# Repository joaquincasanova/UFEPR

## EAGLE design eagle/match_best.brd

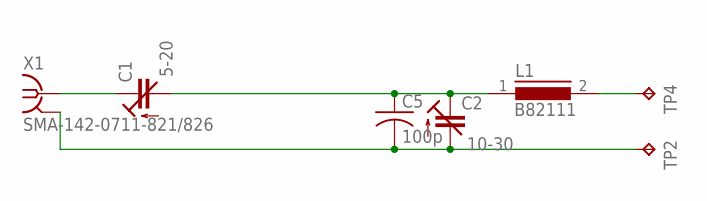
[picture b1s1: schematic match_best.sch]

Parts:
C1: 5-20; SGC3S
C2: 10-30; SGC3S
C5: 100p; 1111
L1: B82111; SUKW1-30
TP2, TP4: TPPAD1-13Y; P1-13Y
X1: SMA-142-0711-821/826; J502-ND-142-0711-821/826

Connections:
unnamed: C1.P$1 (A), C2.P$2 (E), C5.P$1 (1), L1.1
unnamed: C2.P$1 (A), C5.P$2 (2), TP2.TP, X1.G@1 (2), X1.G@2 (2), X1.G@3 (2), X1.G@4 (2)
unnamed: L1.2, TP4.TP
unnamed: C1.P$2 (E), X1.1

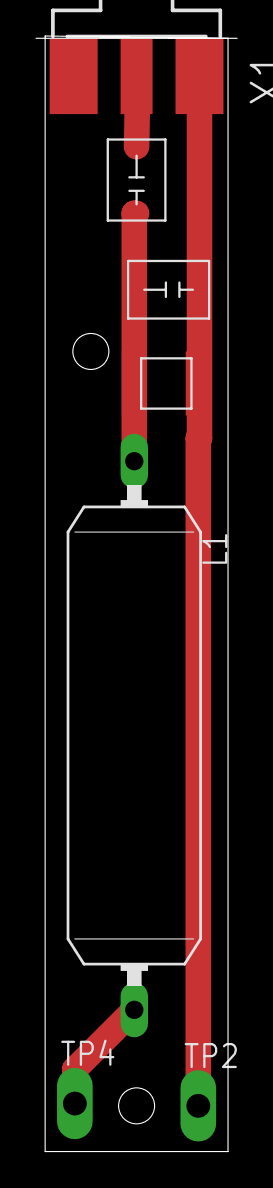
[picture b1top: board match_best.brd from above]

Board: 2 copper layers, 11.2 x 62.0 mm, 7 parts (0 on the bottom side), 4 nets.

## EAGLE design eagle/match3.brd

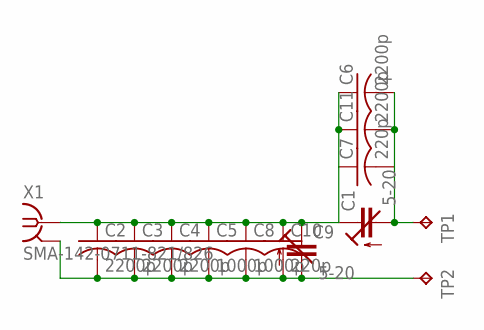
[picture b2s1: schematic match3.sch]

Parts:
C1, C9: 5-20; SGC3S
C2, C3, C4, C6, C11: 2200p; C0805
C5, C8: 1000p; C0805
C7, C10: 220p; C0805
TP1, TP2: TPPAD1-13Y; P1-13Y
X1: SMA-142-0711-821/826; J502-ND-142-0711-821/826

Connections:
unnamed: C1.P$1 (A), C6.2, C7.2, C11.2, TP1.TP
unnamed: C2.2, C3.2, C4.2, C5.2, C8.2, C9.P$1 (A), C10.2, TP2.TP, X1.G@1 (2), X1.G@2 (2), X1.G@3 (2), X1.G@4 (2)
unnamed: C1.P$2 (E), C2.1, C3.1, C4.1, C5.1, C6.1, C7.1, C8.1, C9.P$2 (E), C10.1, C11.1, X1.1

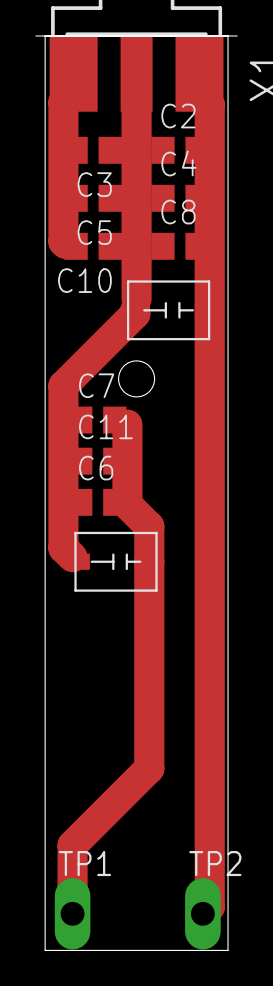
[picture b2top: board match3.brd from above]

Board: 2 copper layers, 11.2 x 50.8 mm, 14 parts (0 on the bottom side), 3 nets.

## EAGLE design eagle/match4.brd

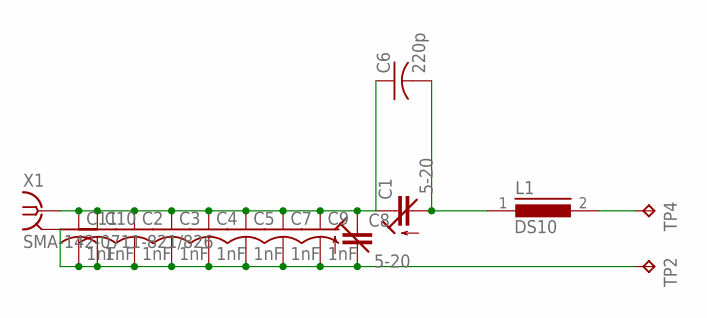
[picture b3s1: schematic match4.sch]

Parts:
C1, C8: 5-20; SGC3S
C2, C3, C4, C5, C7, C9, C10, C11: 1nF; 1111
C6: 220p; 1111
L1: DS10
TP2, TP4: TPPAD1-13Y; P1-13Y
X1: SMA-142-0711-821/826; J502-ND-142-0711-821/826

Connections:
unnamed: C1.P$1 (A), C6.P$2 (2), L1.1
unnamed: C2.P$2 (2), C3.P$2 (2), C4.P$2 (2), C5.P$2 (2), C7.P$2 (2), C8.P$1 (A), C9.P$2 (2), C10.P$2 (2), C11.P$2 (2), TP2.TP, X1.G@1 (2), X1.G@2 (2), X1.G@3 (2), X1.G@4 (2)
unnamed: L1.2, TP4.TP
unnamed: C1.P$2 (E), C2.P$1 (1), C3.P$1 (1), C4.P$1 (1), C5.P$1 (1), C6.P$1 (1), C7.P$1 (1), C8.P$2 (E), C9.P$1 (1), C10.P$1 (1), C11.P$1 (1), X1.1

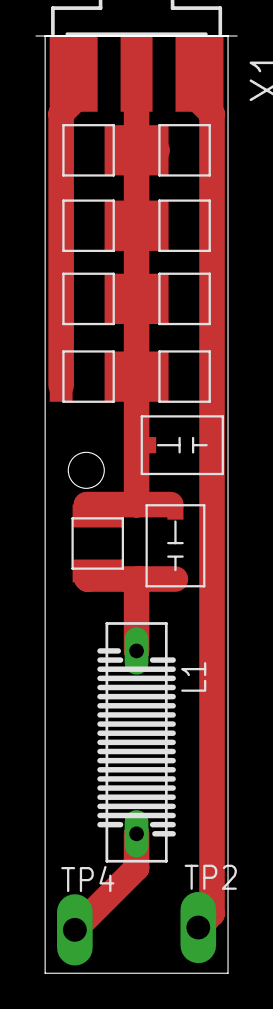
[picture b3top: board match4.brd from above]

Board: 2 copper layers, 11.2 x 52.1 mm, 15 parts (0 on the bottom side), 4 nets.

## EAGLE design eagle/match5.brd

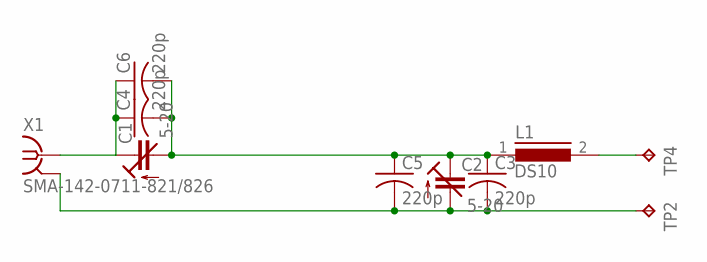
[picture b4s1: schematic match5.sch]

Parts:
C1, C2: 5-20; SGC3S
C3, C4, C5, C6: 220p; C0805
L1: DS10
TP2, TP4: TPPAD1-13Y; P1-13Y
X1: SMA-142-0711-821/826; J502-ND-142-0711-821/826

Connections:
unnamed: C1.P$1 (A), C2.P$2 (E), C3.1, C4.2, C5.1, C6.2, L1.1
unnamed: C2.P$1 (A), C3.2, C5.2, TP2.TP, X1.G@1 (2), X1.G@2 (2), X1.G@3 (2), X1.G@4 (2)
unnamed: L1.2, TP4.TP
unnamed: C1.P$2 (E), C4.1, C6.1, X1.1

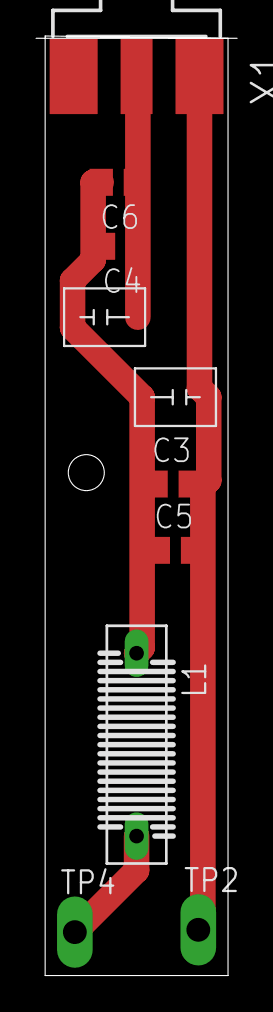
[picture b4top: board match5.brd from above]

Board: 2 copper layers, 11.2 x 52.2 mm, 10 parts (0 on the bottom side), 4 nets.

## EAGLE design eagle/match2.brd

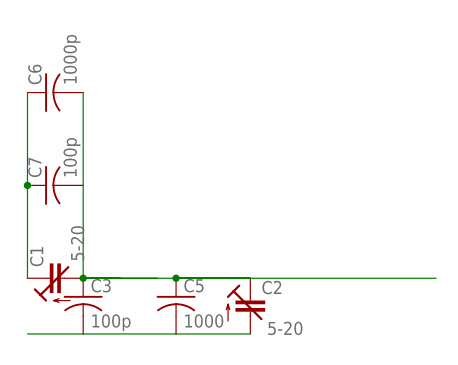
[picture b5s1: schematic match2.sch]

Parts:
C1, C2: 5-20; SGC3S
C3, C7: 100p; C0603
C5: 1000; C0805
C6: 1000p; C0805

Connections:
unnamed: C1.P$1 (A), C2.P$2 (E), C3.1, C5.1, C6.2, C7.2
unnamed: C2.P$1 (A), C3.2, C5.2
unnamed: C1.P$2 (E), C6.1, C7.1

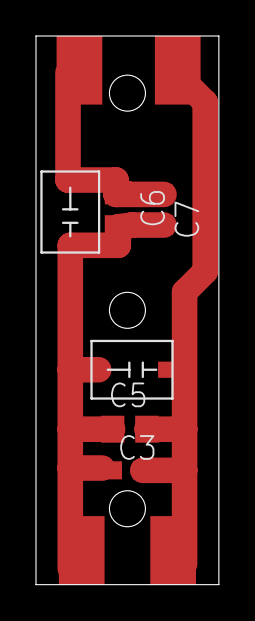
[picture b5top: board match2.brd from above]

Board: 2 copper layers, 10.2 x 30.5 mm, 6 parts (0 on the bottom side), 3 nets.

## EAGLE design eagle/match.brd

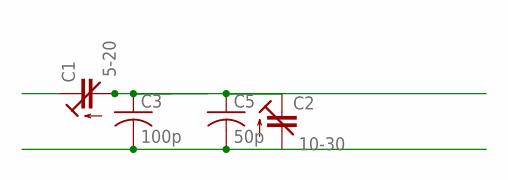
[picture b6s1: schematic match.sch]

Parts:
C1: 5-20; SGC3S
C2: 10-30; SGC3S
C3: 100p; C0805
C5: 50p; C0805

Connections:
unnamed: C1.P$1 (A), C2.P$2 (E), C3.1, C5.1
unnamed: C3.2, C5.2

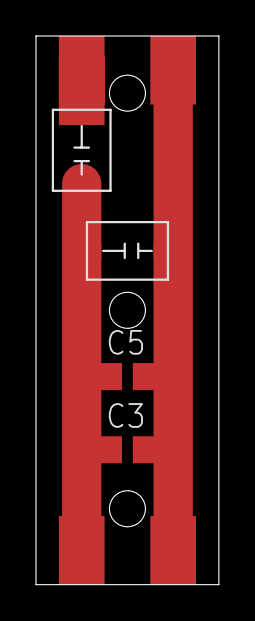
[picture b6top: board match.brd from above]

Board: 2 copper layers, 10.2 x 30.5 mm, 4 parts (0 on the bottom side), 2 nets.

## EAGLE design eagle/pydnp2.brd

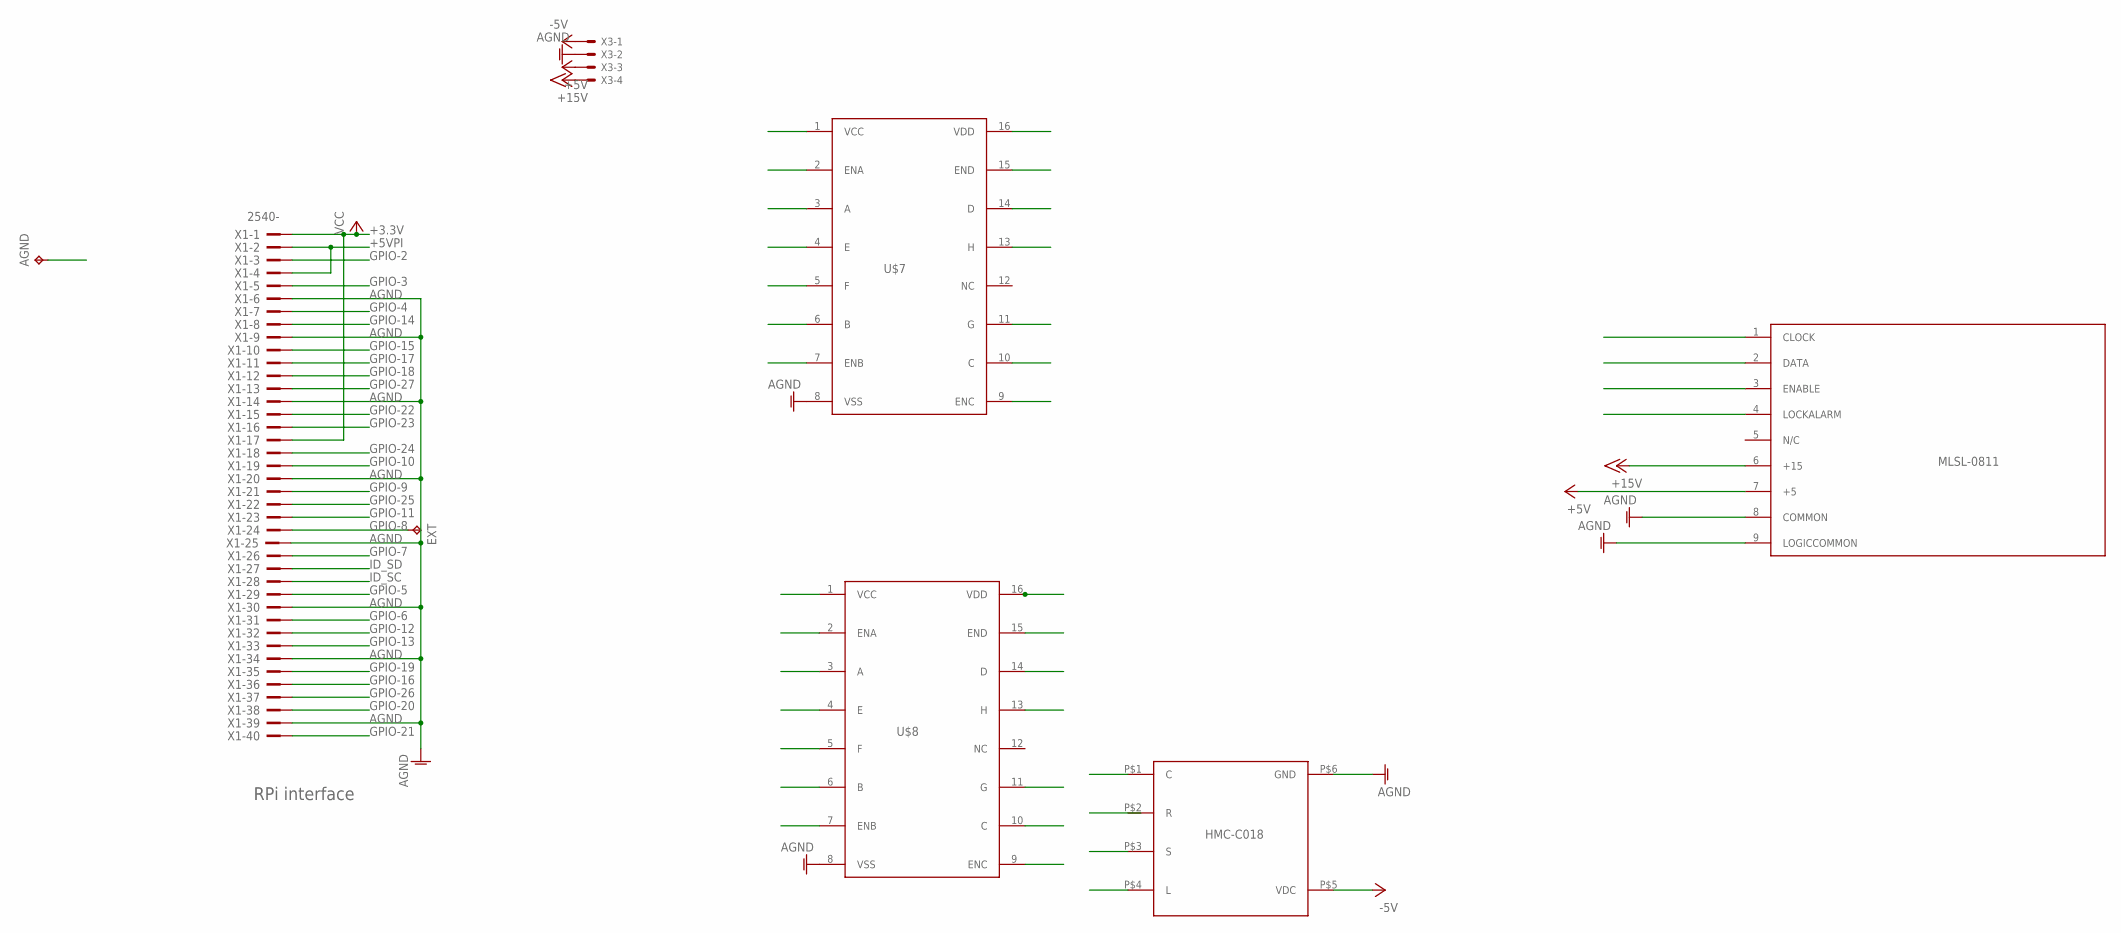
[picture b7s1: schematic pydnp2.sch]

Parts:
AGND: TPPAD1-20Y; P1-20Y
EXT: TPPAD1-20Y; P1-20Y
U$1: MLSLCORRECT; 177-009-FEMALE
U$2: HMC-C018
U$7, U$8: 40109; DIL16
X1: 2540-; PAK100/2500-40
X3: KK-156-4

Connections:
+3.3V: U$7.1 (VCC), U$7.2 (ENA), U$7.7 (ENB), U$7.9 (ENC), U$7.15 (END), U$8.1 (VCC), U$8.2 (ENA), U$8.7 (ENB), U$8.9 (ENC), U$8.15 (END), X1.1, X1.17
+5V: U$1.7 (+5), X3.3
+5VPI: U$7.16 (VDD), U$8.16 (VDD), X1.2, X1.4
+15V: U$1.6 (+15), X3.4
-5V: U$2.P$5 (VDC), X3.1
AGND: AGND.TP, U$1.8 (COMMON), U$1.9 (LOGICCOMMON), U$2.P$6 (GND), U$7.8 (VSS), U$8.8 (VSS), X1.6, X1.9, X1.14, X1.20, X1.25, X1.30, X1.34, X1.39, X3.2
C: U$2.P$1 (C), U$8.4 (E)
CLOCK: U$1.1 (CLOCK), U$7.4 (E)
DATA: U$1.2 (DATA), U$7.13 (H)
ENABLE: U$1.3 (ENABLE), U$7.11 (G)
GPIO-2: X1.3
GPIO-3: X1.5
GPIO-4: U$7.10 (C), X1.7
GPIO-5: X1.29
GPIO-6: X1.31
GPIO-7: X1.26
GPIO-8: EXT.TP, X1.24
GPIO-9: X1.21
GPIO-10: X1.19
GPIO-11: X1.23
GPIO-12: X1.32
GPIO-13: X1.33
GPIO-14: X1.8
GPIO-15: X1.10
GPIO-16: X1.36
GPIO-17: U$7.6 (B), X1.11
GPIO-18: U$8.14 (D), X1.12
GPIO-19: X1.35
GPIO-20: X1.38
GPIO-21: X1.40
GPIO-22: U$7.14 (D), X1.15
GPIO-23: U$8.3 (A), X1.16
GPIO-24: U$8.6 (B), X1.18
GPIO-25: U$8.10 (C), X1.22
GPIO-26: X1.37
GPIO-27: U$7.3 (A), X1.13
ID_SC: X1.28
ID_SD: X1.27
L: U$2.P$4 (L), U$8.5 (F)
LOCK_ALARM: U$1.4 (LOCKALARM), U$7.5 (F)
R: U$2.P$2 (R), U$8.13 (H)
S: U$2.P$3 (S), U$8.11 (G)

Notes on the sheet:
RPi interface
GPIO-27

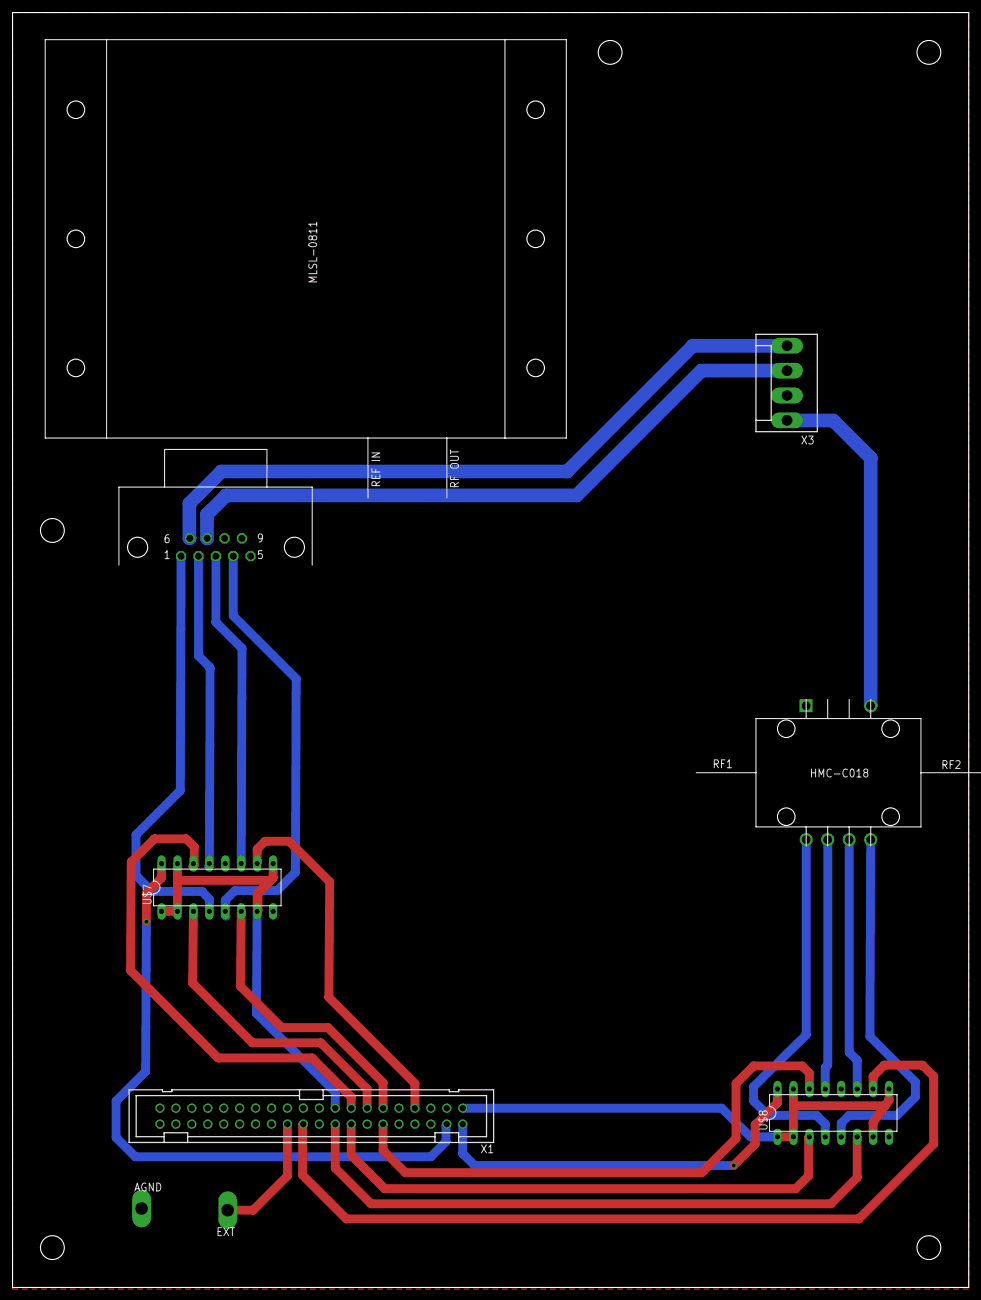
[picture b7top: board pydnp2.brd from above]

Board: 2 copper layers, 152.4 x 203.2 mm, 8 parts (0 on the bottom side), 23 nets.

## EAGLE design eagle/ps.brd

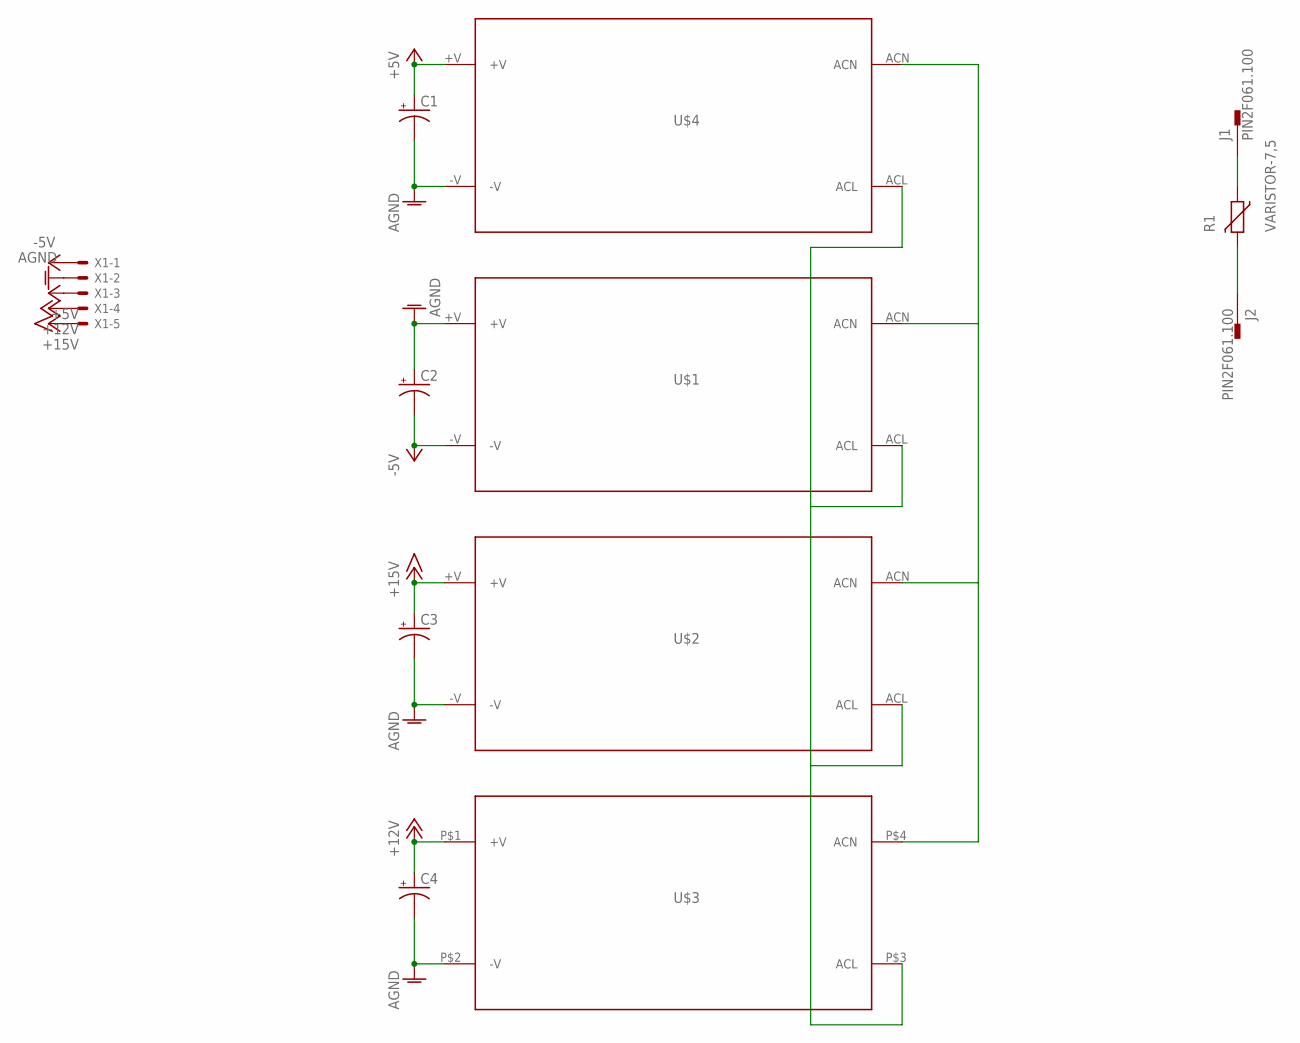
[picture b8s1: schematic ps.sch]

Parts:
C1, C2, C3, C4: CPOL-USE10-22.5; EB22,5D
J1, J2: PIN2F061.100; F061.100
R1: VARISTOR-7,5; R-7,5
U$1, U$4: IRM-30-5; IRM-30-15
U$2: IRM-30-15
U$3: IRM-60-12
X1: KK-156-5

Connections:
+5V: C1.+, U$4.+V, X1.3
+12V: C4.+, U$3.P$1 (+V), X1.4
+15V: C3.+, U$2.+V, X1.5
-5V: C2.-, U$1.-V, X1.1
ACL: J1.A1, J1.A2, R1.1, U$1.ACL, U$2.ACL, U$3.P$3 (ACL), U$4.ACL
ACN: J2.A1, J2.A2, R1.2, U$1.ACN, U$2.ACN, U$3.P$4 (ACN), U$4.ACN
AGND: C1.-, C2.+, C3.-, C4.-, U$1.+V, U$2.-V, U$3.P$2 (-V), U$4.-V, X1.2

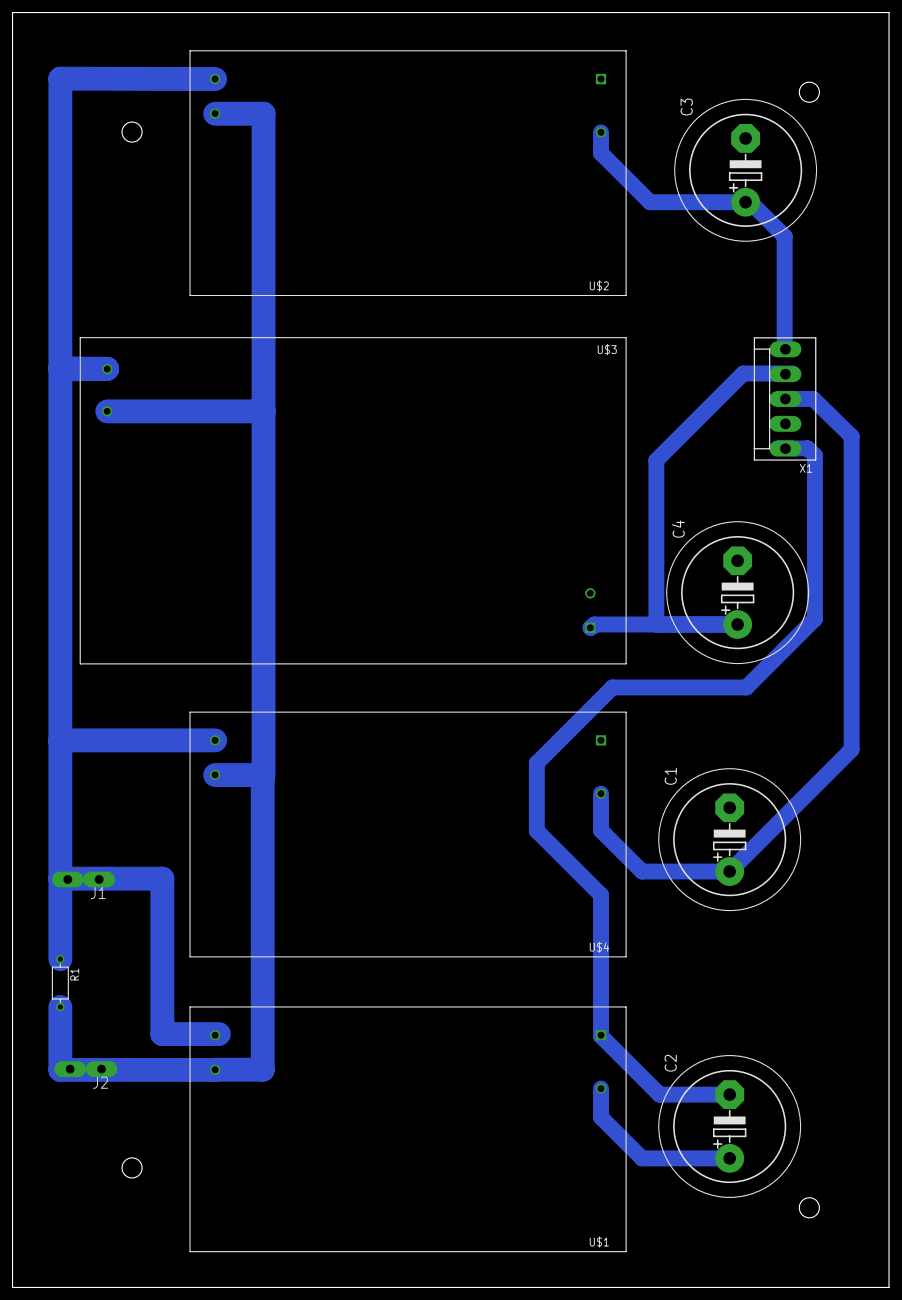
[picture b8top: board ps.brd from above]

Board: 2 copper layers, 139.7 x 203.2 mm, 12 parts (0 on the bottom side), 7 nets.

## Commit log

2015-02-12 new python
2015-08-06 :circus_tent: Added .gitattributes & .gitignore files
2015-09-21 tuna boards
2015-10-13 tuna bored
2015-12-14 asdfg
